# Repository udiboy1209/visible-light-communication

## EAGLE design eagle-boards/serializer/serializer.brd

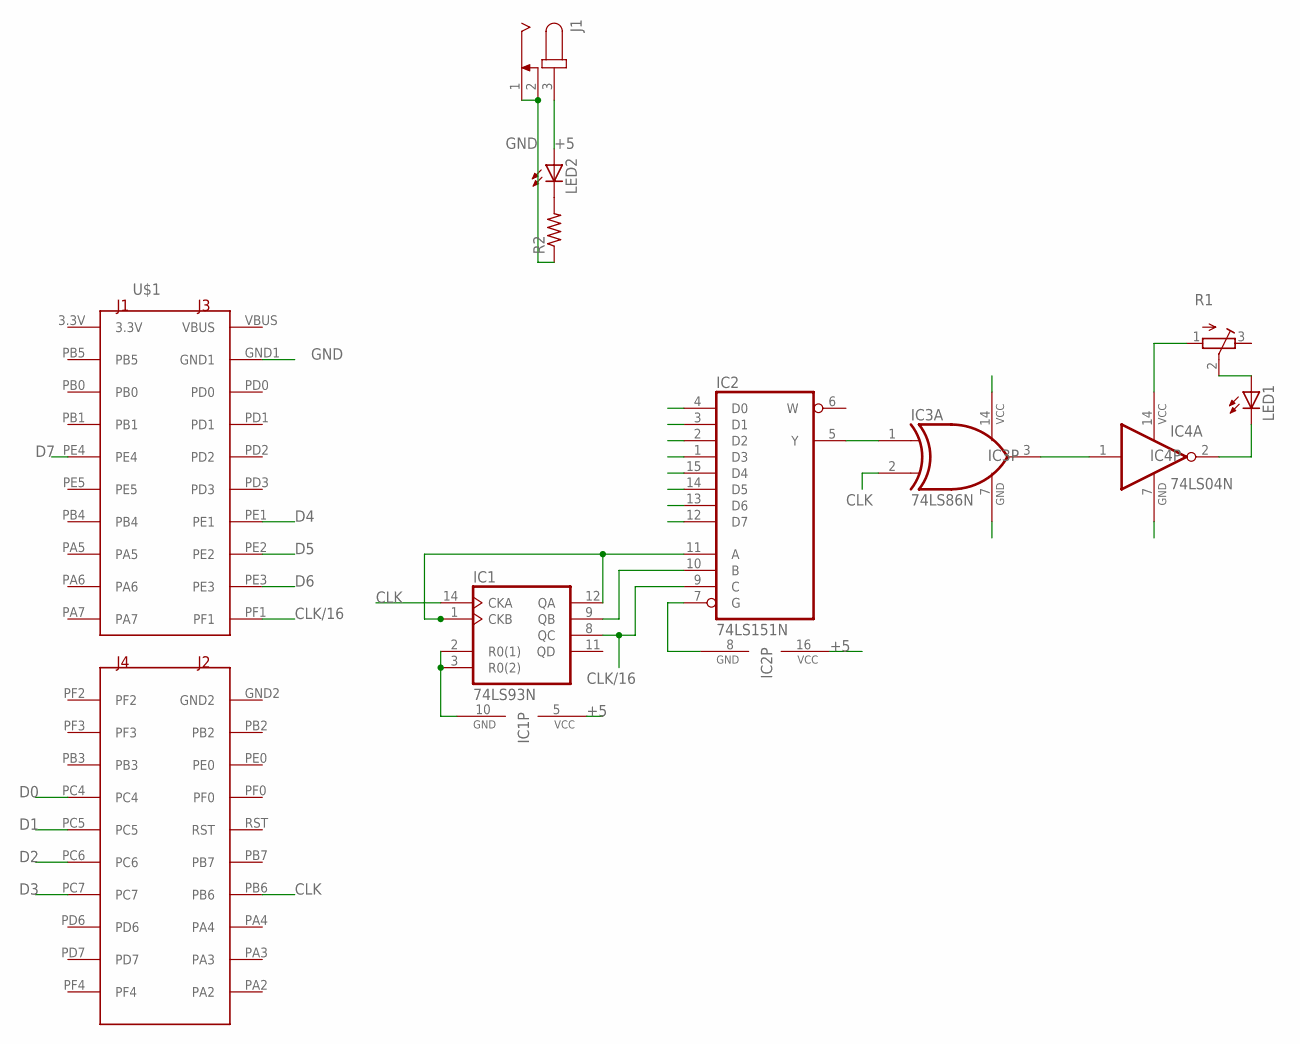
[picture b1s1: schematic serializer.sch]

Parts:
IC1: 74LS93N; DIL14
IC2: 74LS151N; DIL16
IC3: 74LS86N; DIL14
IC4: 74LS04N; DIL14
J1: JACK-PLUG0; SPC4077
LED1, LED2: LED5MM
R1: R-TRIMM3296Y; RTRIM3296Y
R2: R-US_0207/10; 0207/10
U$1: STELLARIS_LAUNCHPAD_BLIZZARD_XL_HEADERS; STELLARISLAUNCHPADHEADERS

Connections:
3.3V: U$1.3.3V
+5: IC1.5 (VCC), IC2.16 (VCC), IC3.14 (VCC), IC4.14 (VCC), J1.3, LED2.A, R1.1 (A)
CLK: IC1.14 (CKA), IC3.2 (I1), U$1.PB6
CLK/16: IC1.8 (QC), IC2.9 (C), U$1.PF1
D0: IC2.4 (D0), U$1.PC4
D1: IC2.3 (D1), U$1.PC5
D2: IC2.2 (D2), U$1.PC6
D3: IC2.1 (D3), U$1.PC7
D4: IC2.15 (D4), U$1.PE1
D5: IC2.14 (D5), U$1.PE2
D6: IC2.13 (D6), U$1.PE3
D7: IC2.12 (D7), U$1.PE4
GND: IC1.2 (R0(1)), IC1.3 (R0(2)), IC1.10 (GND), IC2.7 (G), IC2.8 (GND), IC3.7 (GND), IC4.7 (GND), J1.1, J1.2, R2.1, U$1.GND1
GND2: U$1.GND2
unnamed: IC1.9 (QB), IC2.10 (B)
unnamed: LED2.K (C), R2.2
unnamed: IC1.1 (CKB), IC1.12 (QA), IC2.11 (A)
unnamed: IC3.3 (O), IC4.1 (I)
unnamed: LED1.A, R1.2 (S)
unnamed: IC4.2 (O), LED1.K (C)
RST: U$1.RST
SEROUT: IC2.5 (Y), IC3.1 (I0)
VBUS: U$1.VBUS

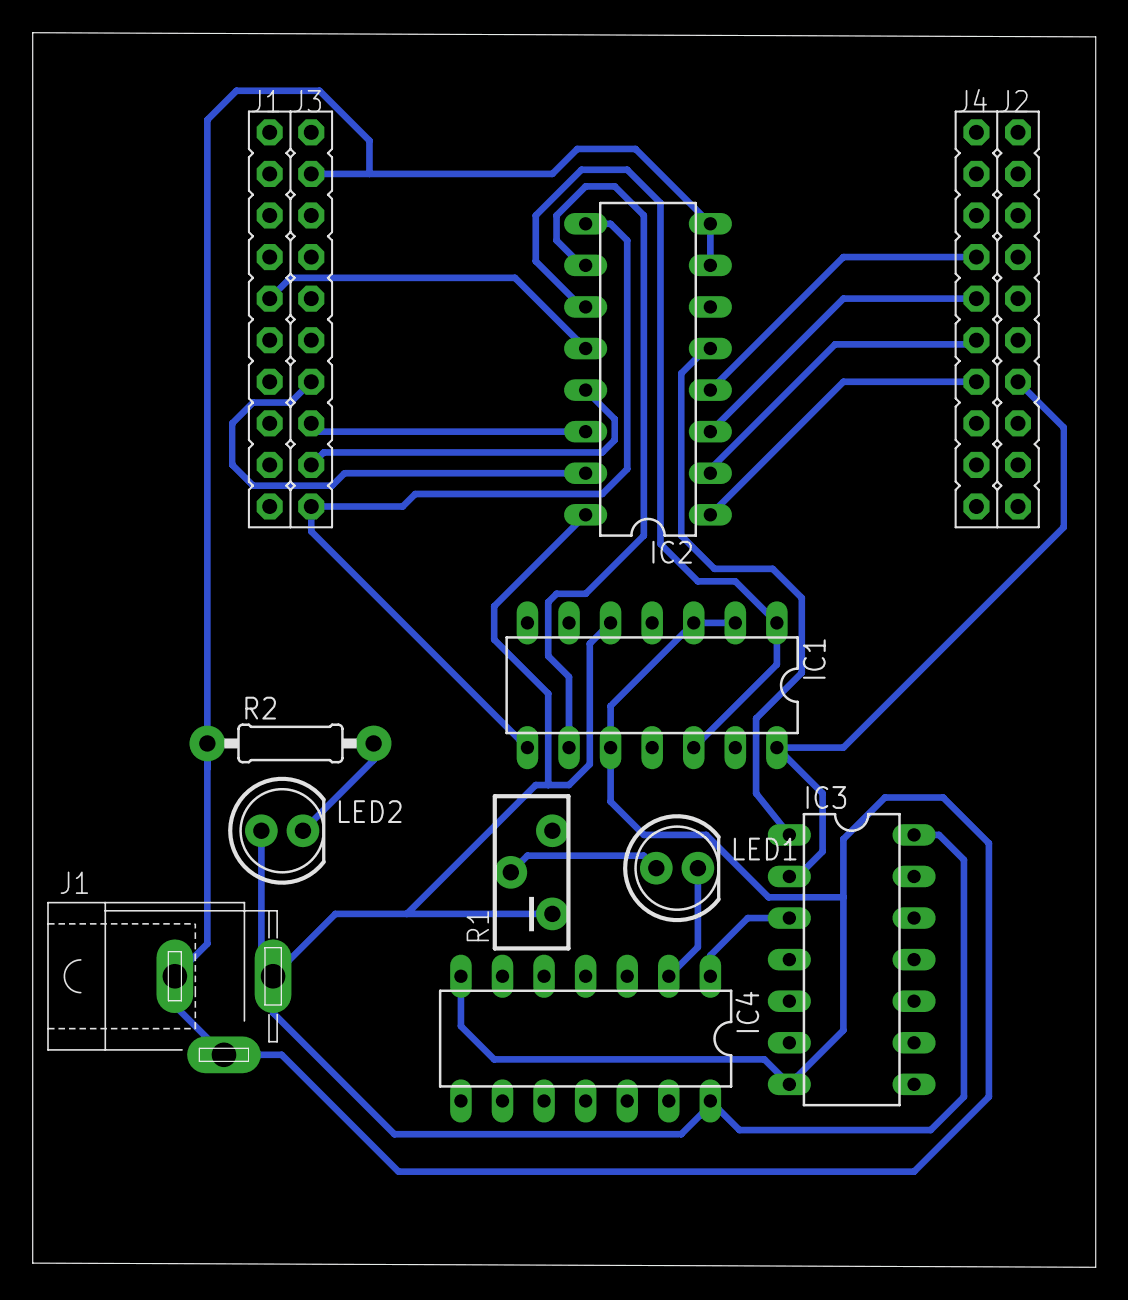
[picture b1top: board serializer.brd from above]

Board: 2 copper layers, 64.9 x 75.4 mm, 10 parts (0 on the bottom side), 19 nets.

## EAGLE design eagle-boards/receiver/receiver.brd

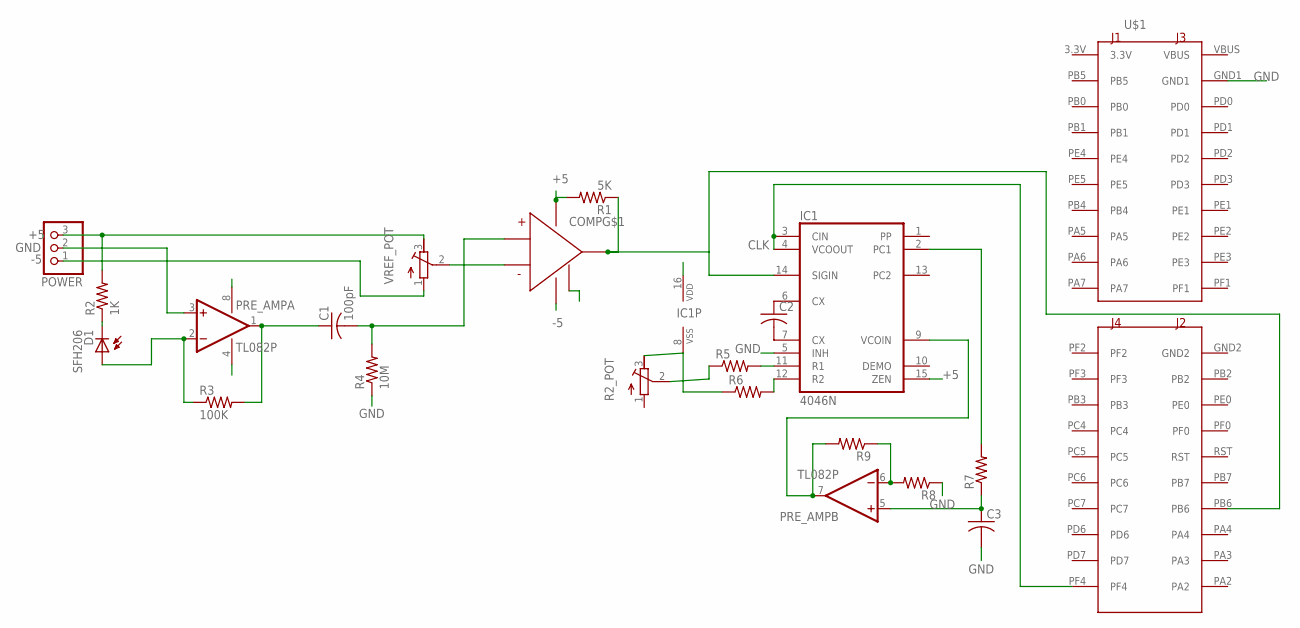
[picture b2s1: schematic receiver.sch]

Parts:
C1: 100pF; C050-025X075
C2, C3: C-US050-025X075; C050-025X075
COMP: LM319; DIL14-1
D1: SFH206
IC1: 4046N; DIL16
POWER: PINHD-1X3; 1X03
PRE_AMP: TL082P; DIL08
R1: 5K; 0207/10
R2: 1K; 0207/10
R2_POT: R-TRIMM3296Y; RTRIM3296Y
R3: 100K; 0207/10
R4: 10M; 0207/10
R5, R6, R7, R8, R9: R-US_0207/10; 0207/10
U$1: STELLARIS_LAUNCHPAD_BLIZZARD_XL_HEADERS; STELLARISLAUNCHPADHEADERS
VREF_POT: R-TRIMM3296Y; RTRIM3296Y

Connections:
3.3V: U$1.3.3V
+5: COMP.P11 (VCC), IC1.15 (ZEN), IC1.16 (VDD), POWER.3, PRE_AMP.8 (V+), R1.2, R2.2, VREF_POT.3 (E)
-5: COMP.P6 (GND), POWER.1, PRE_AMP.4 (V-), VREF_POT.1 (A)
A: D1.A, PRE_AMP.2 (-IN), R3.1
AMP_OUT: C1.1, PRE_AMP.1 (OUT), R3.2
CLK: IC1.3 (CIN), IC1.4 (VCOOUT), U$1.PF4
DATA_OUT: COMP.P12 (OUT), IC1.14 (SIGIN), R1.1, U$1.PB6
FILTER_OUT: C1.2, COMP.P4 (NONINV), R4.2
GND: C3.2, COMP.P3 (GND2), IC1.5 (INH), IC1.8 (VSS), POWER.2, PRE_AMP.3 (+IN), R2_POT.3 (E), R4.1, R6.1, R8.1, U$1.GND1
GND2: U$1.GND2
unnamed: R2_POT.2 (S), R5.1
unnamed: IC1.11 (R1), R5.2
unnamed: IC1.12 (R2), R6.2
unnamed: C2.1, IC1.6 (CX)
unnamed: D1.K (C), R2.1
unnamed: C2.2, IC1.7 (CX)
unnamed: IC1.9 (VCOIN), PRE_AMP.7 (OUT), R9.2
unnamed: C3.1, PRE_AMP.5 (+IN), R7.1
unnamed: IC1.2 (PC1), R7.2
unnamed: PRE_AMP.6 (-IN), R8.2, R9.1
RST: U$1.RST
THRESH: COMP.P5 (INV), VREF_POT.2 (S)
VBUS: U$1.VBUS

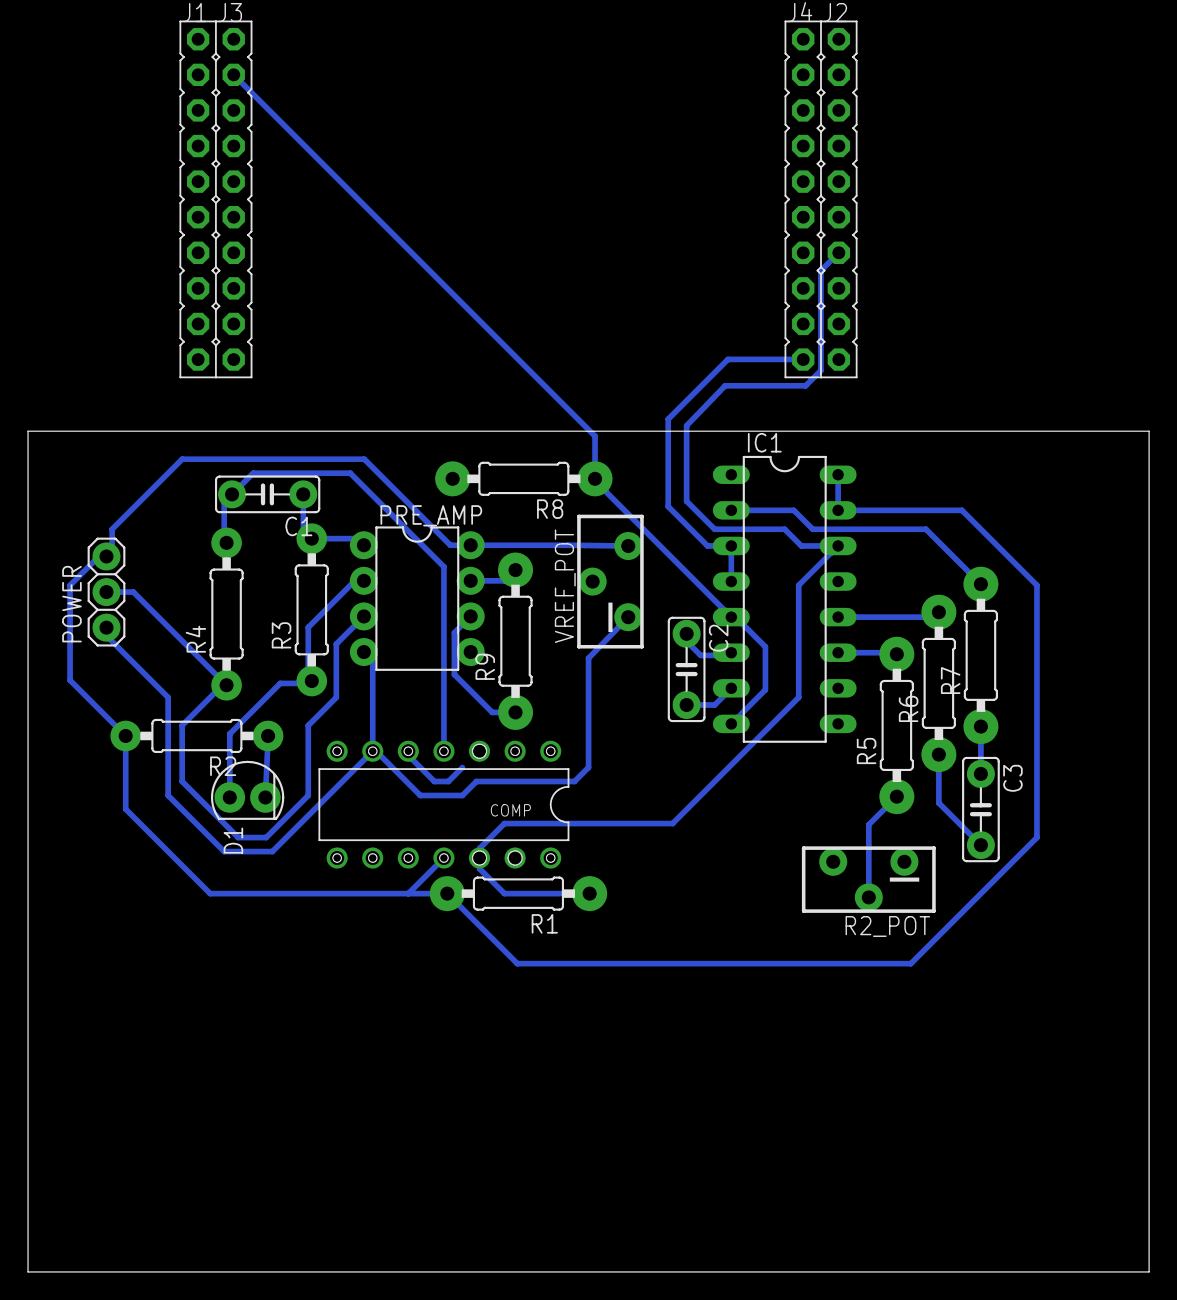
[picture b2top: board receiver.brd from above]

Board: 2 copper layers, 80.0 x 60.0 mm, 20 parts (0 on the bottom side), 19 nets.

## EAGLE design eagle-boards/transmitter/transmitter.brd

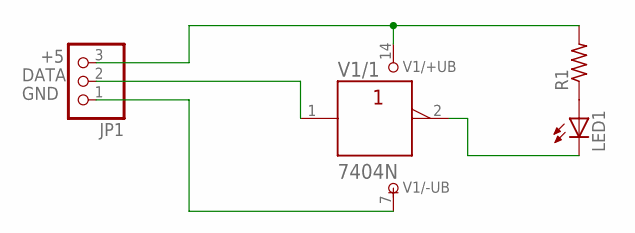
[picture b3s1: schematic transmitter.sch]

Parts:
JP1: PINHD-1X3; 1X03
LED1: LED5MM
R1: R-US_0207/10; 0207/10
V1: 7404N; DIL14

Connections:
+5: JP1.3, R1.2, V1.14 (+UB)
DATA: JP1.2, V1.1 (A)
DATA_BAR: LED1.K (C), V1.2 (Y)
GND: JP1.1, V1.7 (-UB)
unnamed: LED1.A, R1.1

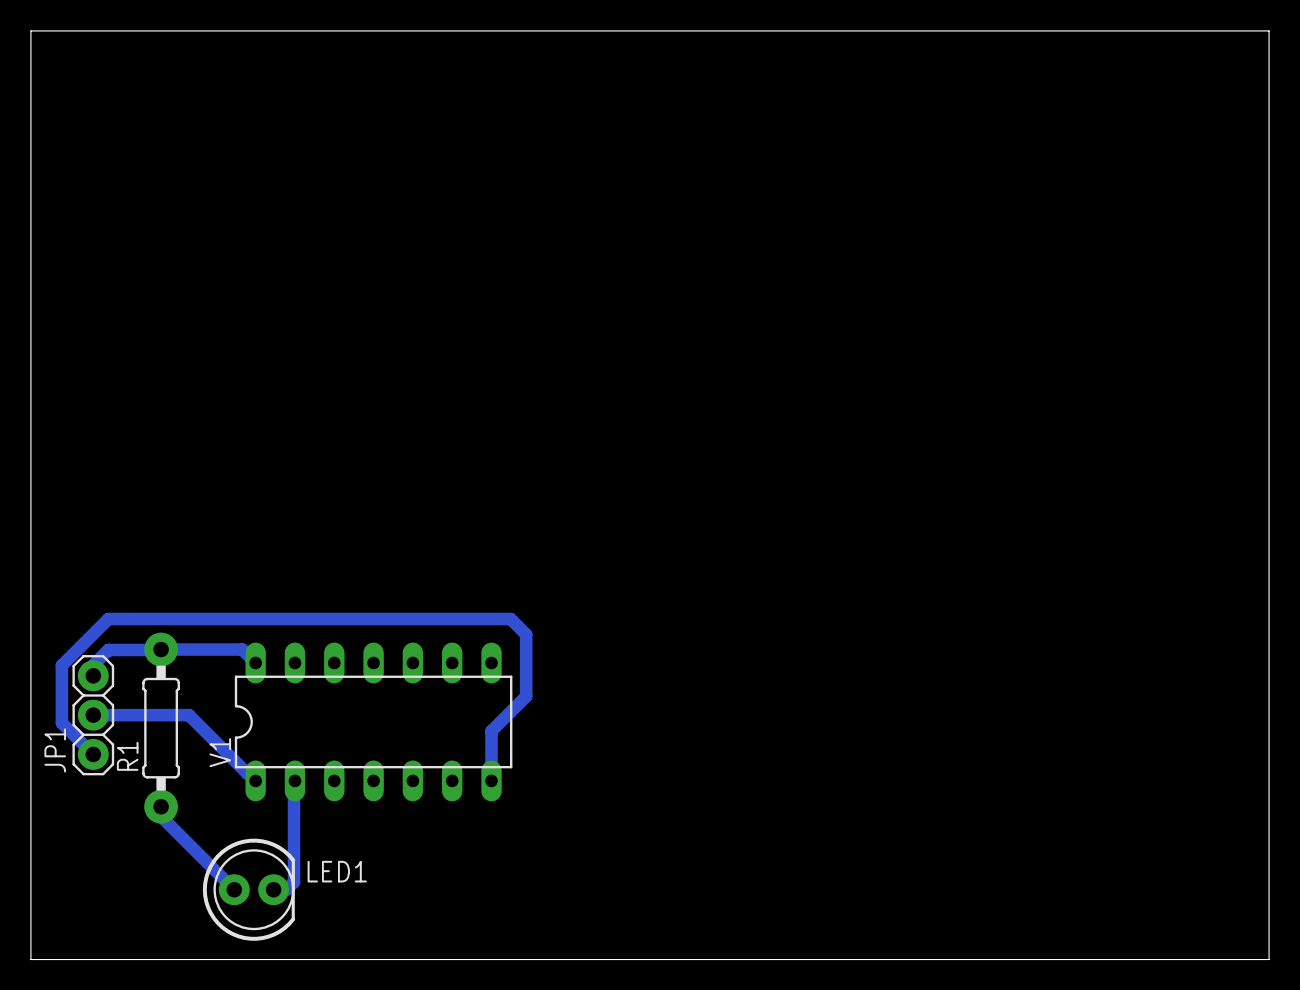
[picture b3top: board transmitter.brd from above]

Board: 2 copper layers, 80.0 x 60.0 mm, 4 parts (0 on the bottom side), 5 nets.

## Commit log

2017-03-29 Initialise repo
2017-04-03 Transmit code working with PLL
